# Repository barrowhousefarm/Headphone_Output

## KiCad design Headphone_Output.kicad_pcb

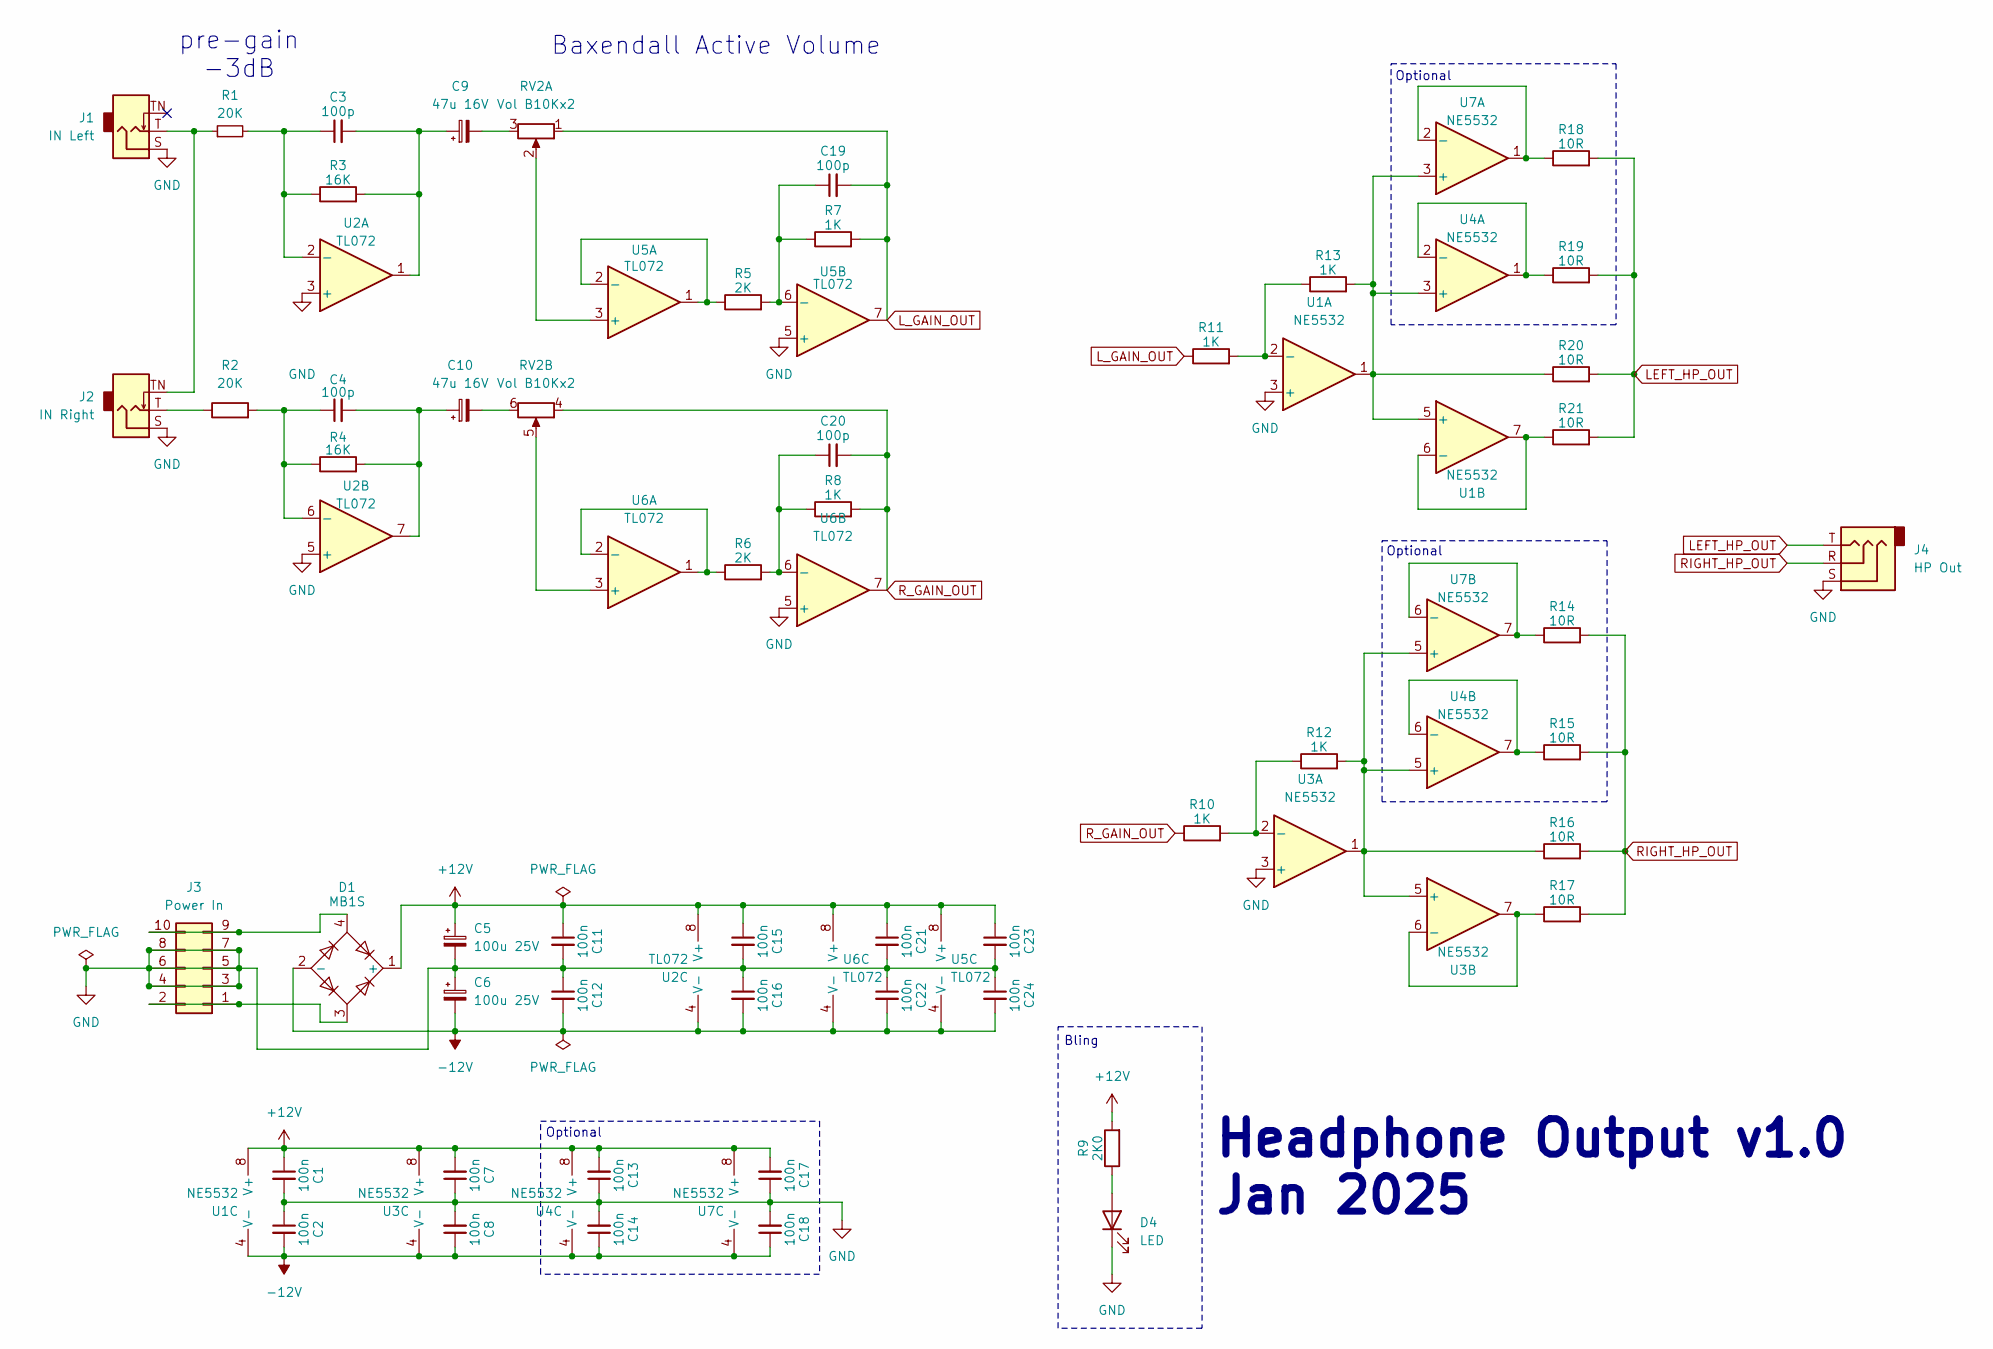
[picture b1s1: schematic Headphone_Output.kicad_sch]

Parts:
C1, C2, C7, C8, C11, C12, C13, C14, C15, C16, C17, C18, C21, C22, C23, C24: 100n; C_1206_3216Metric
C3, C4, C19, C20: 100p; C_1206_3216Metric
C5, C6: 100u 25V; CP_Elec_6.3x7.7
C9, C10: 47u 16V; CP_Elec_5x5.4
D1: MB1S; SOP-4_3.8x4.1mm_P2.54mm
D4: LED; LED_1206_3216Metric_ReverseMount_Hole1.8x2.4mm
J1: IN Left; Jack_3.5mm_QingPu_WQP-PJ301M-12_Vertical
J2: IN Right; Jack_3.5mm_QingPu_WQP-PJ301M-12_Vertical
J3: Power In; IDC-Header_2x05_P2.54mm_Vertical
J4: HP Out; Jack_3.5mm_QingPu_WQP-PJ366ST_Vertical
R1, R2: 20K; R_1206_3216Metric
R3, R4: 16K; R_1206_3216Metric
R5, R6: 2K; R_1206_3216Metric
R7, R8, R10, R11, R12, R13: 1K; R_1206_3216Metric
R9: 2K0; R_1206_3216Metric
R14, R15, R16, R17, R18, R19, R20, R21: 10R; R_1206_3216Metric
RV2: Vol B10Kx2; Potentiometer_Bourns_PTV112-4_Dual_Vertical
U1, U3, U4, U7: NE5532; SOP-8_3.76x4.96mm_P1.27mm
U2, U5, U6: TL072; SOP-8_3.76x4.96mm_P1.27mm

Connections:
+12V: C1.1, C5.1, C7.2, C11.1, C13.2, C15.1, C17.2, C21.1, C23.1, D1.1 (+), R9.2, U1.8 (V+), U2.8 (V+), U3.8 (V+), U4.8 (V+), U5.8 (V+), U6.8 (V+), U7.8 (V+)
-12V: C2.2, C6.2, C8.1, C12.2, C14.1, C16.2, C18.1, C22.2, C24.2, D1.2 (-), U1.4 (V-), U2.4 (V-), U3.4 (V-), U4.4 (V-), U5.4 (V-), U6.4 (V-), U7.4 (V-)
GND: C1.2, C2.1, C5.2, C6.1, C7.1, C8.2, C11.2, C12.1, C13.1, C14.2, C15.2, C16.1, C17.1, C18.2, C21.2, C22.1, C23.2, C24.1, D4.1 (K), J1.S, J2.S, J3.3, J3.4, J3.5, J3.6, J3.7, J3.8, J4.S, U1.3 (+), U2.3 (+), U2.5 (+), U3.3 (+), U5.5 (+), U6.5 (+)
LEFT_HP_OUT: J4.T, R18.2, R19.2, R20.2, R21.2
L_GAIN_OUT: C19.2, R7.2, R11.1, RV2.1, U5.7
unnamed: C3.2, C9.1, R3.2, U2.1
unnamed: C9.2, RV2.3
unnamed: C4.2, C10.1, R4.2, U2.7
unnamed: C10.2, RV2.6
unnamed: D4.2 (A), R9.1
unnamed: J1.T, J2.TN, R1.1
unnamed: J2.T, R2.1
unnamed: D1.3, J3.1, J3.2
unnamed: D1.4, J3.9, J3.10
unnamed: R11.2, R13.1, U1.2 (-)
unnamed: R13.2, R20.1, U1.1, U1.5 (+), U4.3 (+), U7.3 (+)
unnamed: R21.1, U1.6 (-), U1.7
unnamed: C3.1, R1.2, R3.1, U2.2 (-)
unnamed: C4.1, R2.2, R4.1, U2.6 (-)
unnamed: R10.2, R12.1, U3.2 (-)
unnamed: R12.2, R16.1, U3.1, U3.5 (+), U4.5 (+), U7.5 (+)
unnamed: R17.1, U3.6 (-), U3.7
unnamed: R19.1, U4.1, U4.2 (-)
unnamed: R15.1, U4.6 (-), U4.7
unnamed: RV2.2, U5.3 (+)
unnamed: R5.1, U5.1, U5.2 (-)
unnamed: C19.1, R5.2, R7.1, U5.6 (-)
unnamed: RV2.5, U6.3 (+)
unnamed: R6.1, U6.1, U6.2 (-)
unnamed: C20.1, R6.2, R8.1, U6.6 (-)
unnamed: R18.1, U7.1, U7.2 (-)
unnamed: R14.1, U7.6 (-), U7.7
RIGHT_HP_OUT: J4.R, R14.2, R15.2, R16.2, R17.2
R_GAIN_OUT: C20.2, R8.2, R10.1, RV2.4, U6.7

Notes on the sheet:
pre-gain -3dB
Bling
Baxendall Active Volume
Optional
Headphone Output v1.0 Jan 2025

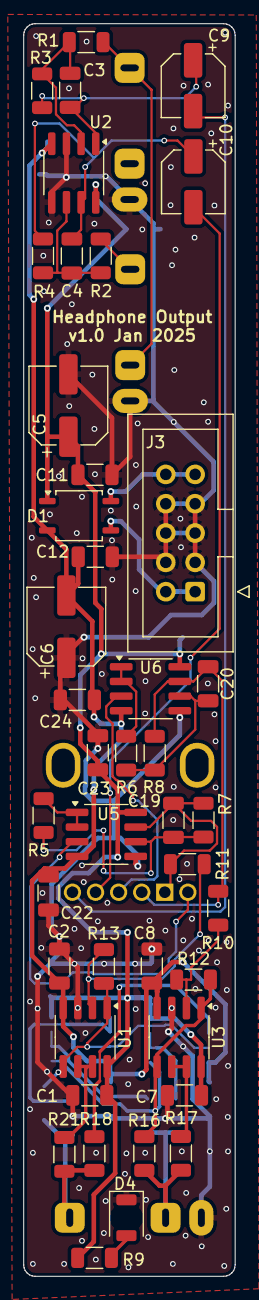
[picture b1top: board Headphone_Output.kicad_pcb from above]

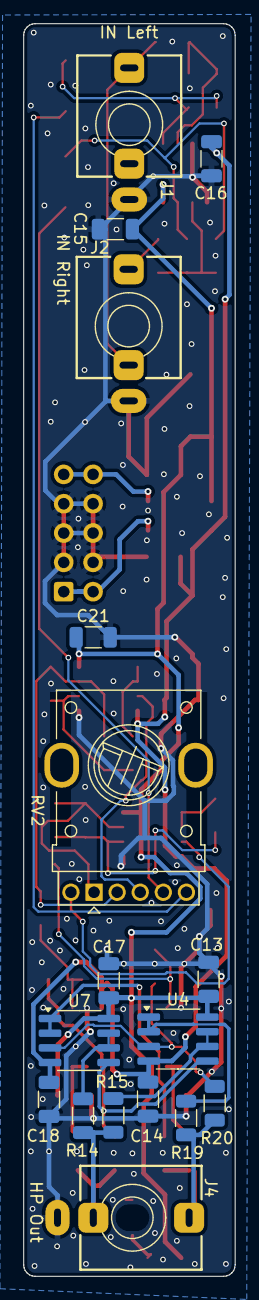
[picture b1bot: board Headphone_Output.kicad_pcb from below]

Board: 2 copper layers, 18.3 x 108.5 mm, 59 parts (17 on the bottom side), 34 nets.

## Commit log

2025-01-26 Add files via upload
    First upload.. folders to do
2025-01-26 Add files via upload
    front panel
2025-01-26 Add files via upload
    interactive BOM
